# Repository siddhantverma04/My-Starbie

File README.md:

# My Starbie
This is my very own starbie made for HackClub's Half life program. 
## What is it?
I made it as a simple digital pet to stay on my desk. I also made it shaped like a controller with the switches on the sides so it feels like an real controller. 
## How'd I make it?
To make it I used KiCad for the PCB. And the arduino software for the firmware.
## How should you assemble it for yourself?
To build it for your self make sure you have all of the parts in the BOM, and solder them onto the PCB in the right orientations. After soldering you can download the firmware and flash it onto the ESP32C3 by holding down the boot button while plugging it into your computer. Then you use any method to flash it on.

## Schematic:

## PCB

## 3D view

## BOM

| Item | Qty | Supplier | Cost/item | Total Cost |
| :--- | :---: | :--- | :---: | :---: |
| [0.96 OLED](https://www.amazon.com/gp/product/B07FK8GB8T/ref=ox_sc_act_title_3?smid=A3CX4TQNUXMB0L&psc=1) | 1 | amazon | $5.99 | $5.99 |
| [DHT11](https://www.amazon.com/gp/product/B0CRRXJ83F/ref=ox_sc_act_title_5?smid=AGBPQLQT372PL&psc=1) | 1 | amazon | $3.78 | $3.78 |
| [10k Resistor](https://www.amazon.com/gp/product/B0BDKY8VQG/ref=ox_sc_act_title_1?smid=A2XLLJ8HYD6SMA&psc=1) | 100 | amazon | $0.04 | $4.00 |
| [MX Switches](https://www.amazon.com//dp/B0FQP8VYX4) | 2 | amazon | $0.18 | $8.99 |
| [Keycaps](https://www.amazon.com/dp/B0CQ2VLMVY) | 2 | amazon | $0.60 | $11.99 |
| [PCB](https://www.jlcpcb.com/) | 5 | JLCPCB | $1.58 | $7.90 |
| Estimated total shipping | 1 | — | — | $8.00 |
| **Total Project Cost** | | | | **$44.36** |

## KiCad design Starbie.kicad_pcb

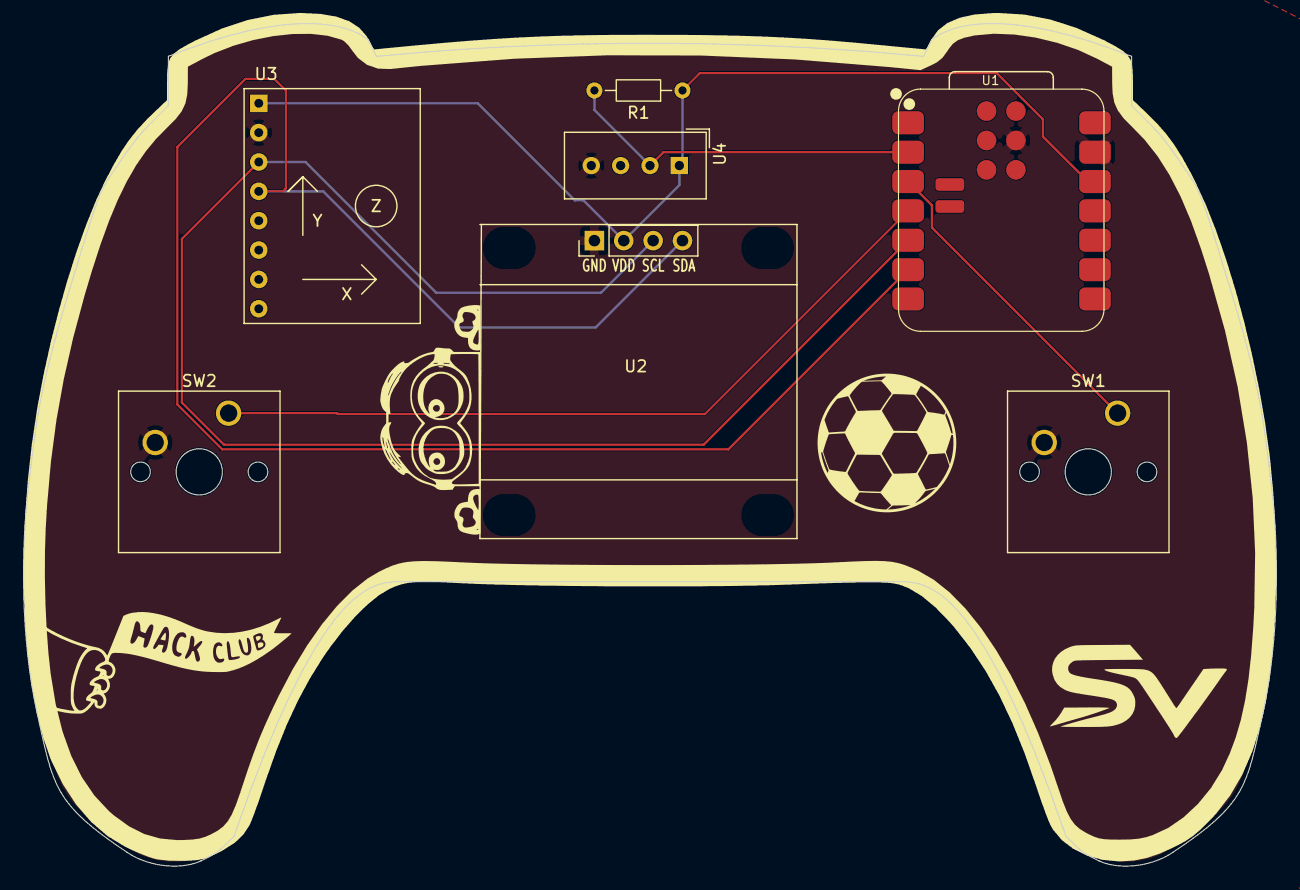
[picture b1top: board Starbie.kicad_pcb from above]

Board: 2 copper layers, 108.4 x 72.9 mm, 7 parts (0 on the bottom side), 7 nets.

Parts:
R1: 10k; R_Axial_DIN0204_L3.6mm_D1.6mm_P7.62mm_Horizontal
SW1, SW2: SW_Push; SW_Cherry_MX_1.00u_PCB
U1: XIAO-ESP32-C3-SMD
U2: Display_128x64_096_I2C
U3: MPU6050_Module
U4: DHT11; Aosong_DHT11_5.5x12.0_P2.54mm

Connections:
+3.3V: R1.1, U1.12 (3V3_OUT), U2.2 (VCC), U3.1 (VCC), U4.1 (VDD)
/DHT11 DATA: R1.2, U1.2 (D1), U4.2 (DATA)
/GPIO2: SW1.1, U1.3 (D2)
/GPIO3: SW2.1, U1.4 (D3)
/SCL: U1.5 (D4), U2.3 (SCL), U3.3 (SCL)
/SDA: U1.6 (D5), U2.4 (SDA), U3.4 (SDA)
GND: SW1.2, SW2.2, U1.13 (GND), U1.18 (GND), U2.1 (GND), U3.2 (GND), U4.4 (GND)
